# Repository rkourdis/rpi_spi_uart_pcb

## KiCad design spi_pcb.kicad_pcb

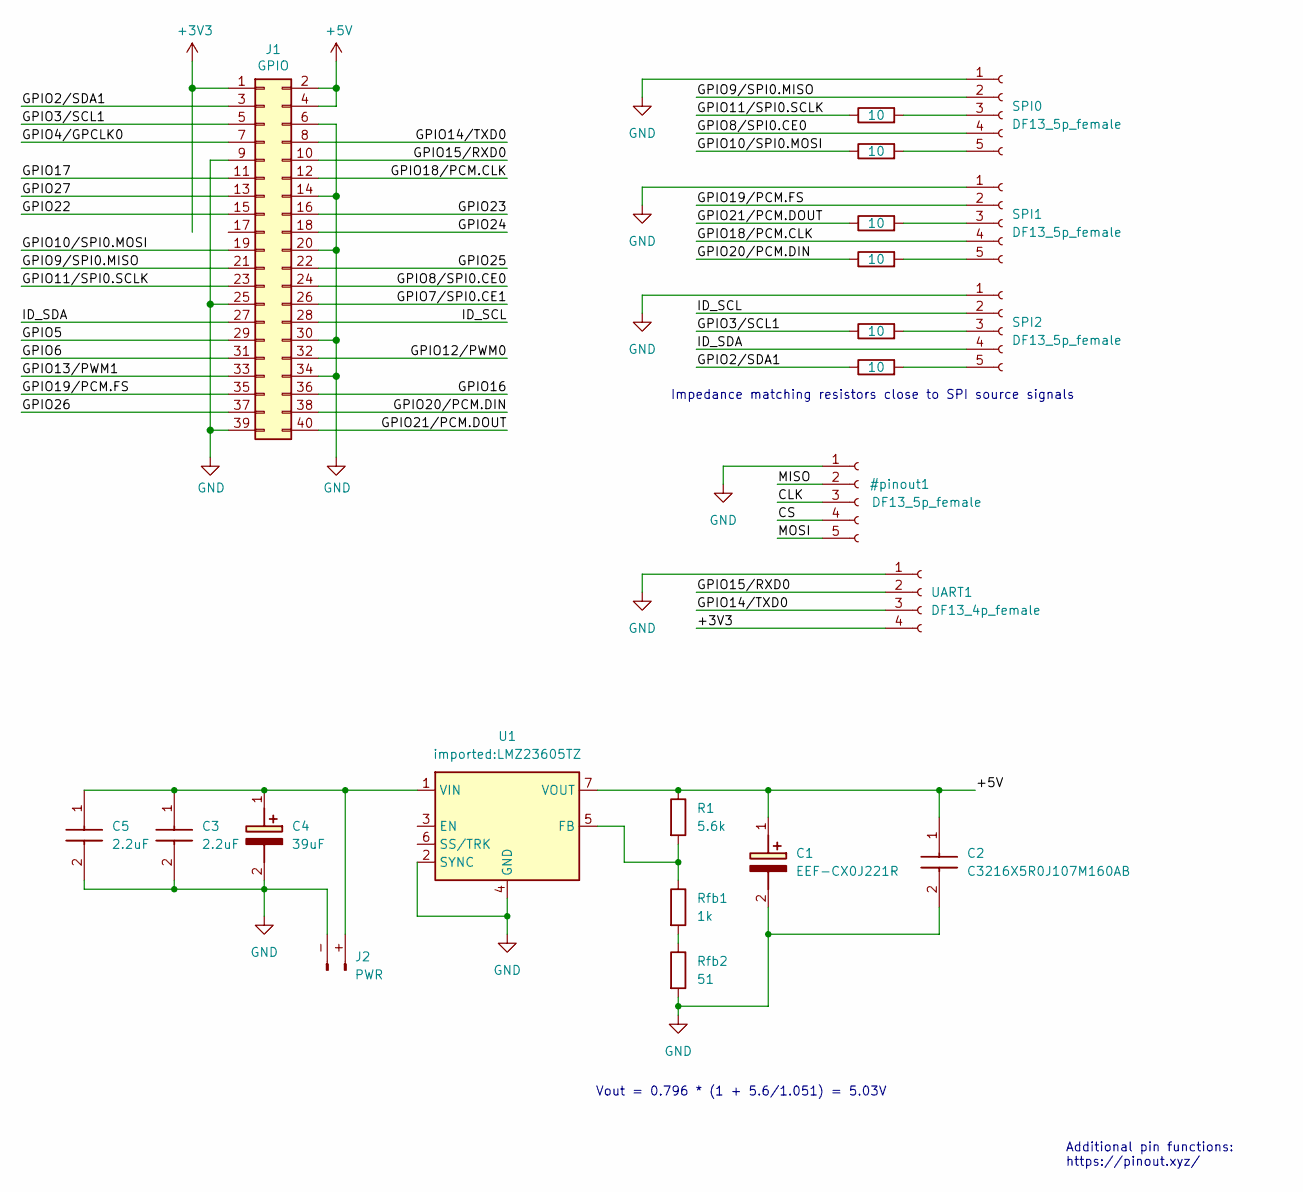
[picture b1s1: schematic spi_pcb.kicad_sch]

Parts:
C1: EEF-CX0J221R; EEFCX0J101R; Mouser Part Number 667-EEF-CX0J221R
C2: C3216X5R0J107M160AB; CAPC3216X180N; Mouser Part Number 810-C3216X5R0J107M
C3, C5: 2.2uF; CAPC1608X90N; Mouser Part Number 81-GRT188R61H225KE3D
C4: 39uF; 16SVPT560M; Manufacturer_Part_Number 50SVPF39M; Mouser Part Number 667-50SVPF39M
J1: GPIO; PinSocket_2x20_P2.54mm_Vertical
J2: PWR; AMASS_XT30PW-M_1x02_P2.50mm_Horizontal
R1: 5.6k; R_0603_1608Metric
R3, R4, R5, R6, R7, R8: 10; R_0402_1005Metric_Pad0.72x0.64mm_HandSolder
Rfb1: 1k; R_0603_1608Metric
Rfb2: 51; R_0603_1608Metric
SPI0, SPI1, SPI2: DF13_5p_female; Hirose_DF13-05P-1.25DS_1x05_P1.25mm_Horizontal
U1: imported:LMZ23605TZ; Texas_NDW-7_TabPin4
UART1: DF13_4p_female; Hirose_DF13-04P-1.25DS_1x04_P1.25mm_Horizontal

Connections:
+3V3: J1.1, UART1.4
+5V: C1.1 (+), C2.1, J1.2, J1.4, R1.1, U1.7 (VOUT)
/GPIO2/SDA1: J1.3, R8.1
/GPIO3/SCL1: J1.5, R7.1
/GPIO4/GPCLK0: J1.7
/GPIO5: J1.29
/GPIO6: J1.31
/GPIO7/SPI0.CE1: J1.26
/GPIO8/SPI0.CE0: J1.24, SPI0.4
/GPIO9/SPI0.MISO: J1.21, SPI0.2
/GPIO10/SPI0.MOSI: J1.19, R4.1
/GPIO11/SPI0.SCLK: J1.23, R3.1
/GPIO12/PWM0: J1.32
/GPIO13/PWM1: J1.33
/GPIO14/TXD0: J1.8, UART1.3
/GPIO15/RXD0: J1.10, UART1.2
/GPIO16: J1.36
/GPIO17: J1.11
/GPIO18/PCM.CLK: J1.12, SPI1.4
/GPIO19/PCM.FS: J1.35, SPI1.2
/GPIO20/PCM.DIN: J1.38, R5.1
/GPIO21/PCM.DOUT: J1.40, R6.1
/GPIO22: J1.15
/GPIO23: J1.16
/GPIO24: J1.18
/GPIO25: J1.22
/GPIO26: J1.37
/GPIO27: J1.13
/ID_SCL: J1.28, SPI2.2
/ID_SDA: J1.27, SPI2.4
GND: C1.2 (-), C2.2, C3.2, C4.2 (-), C5.2, J1.6, J1.9, J1.14, J1.20, J1.25, J1.30, J1.34, J1.39, J2.- (Pin_1), Rfb2.2, SPI0.1, SPI1.1, SPI2.1, U1.2 (SYNC), U1.4 (GND), UART1.1
unnamed: C3.1, C4.1 (+), C5.1, J2.+ (Pin_2), U1.1 (VIN)
unnamed: Rfb1.2, Rfb2.1
unnamed: R3.2, SPI0.3
unnamed: R4.2, SPI0.5
unnamed: R6.2, SPI1.3
unnamed: R5.2, SPI1.5
unnamed: R7.2, SPI2.3
unnamed: R8.2, SPI2.5
unnamed: R1.2, Rfb1.1, U1.5 (FB)

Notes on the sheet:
Additional pin functions: https://pinout.xyz/
Impedance matching resistors close to SPI source signals
Vout = 0.796 * (1 + 5.6/1.051) = 5.03V

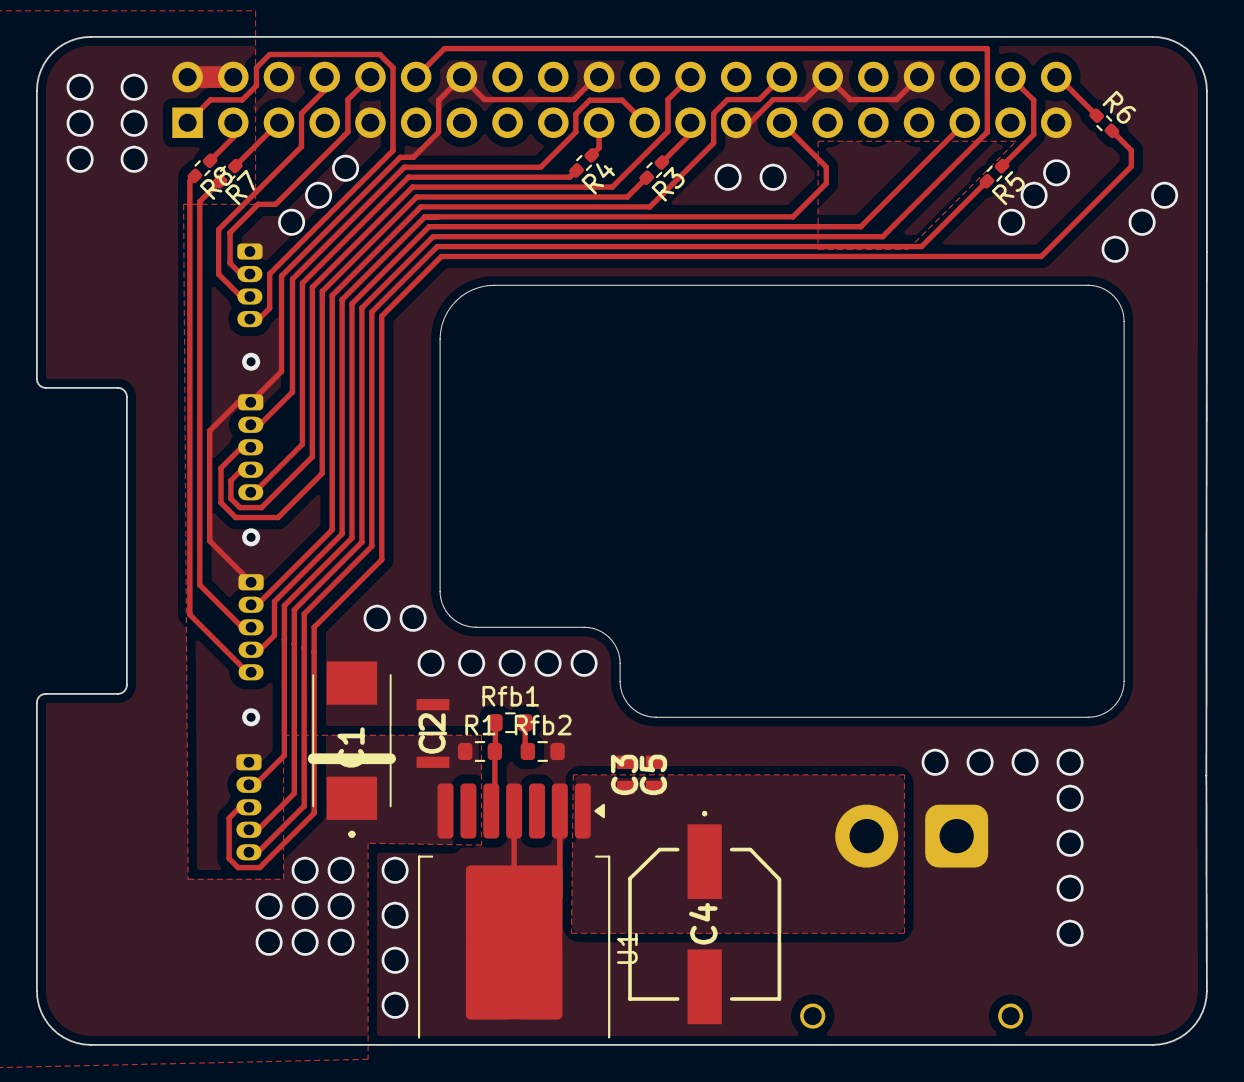
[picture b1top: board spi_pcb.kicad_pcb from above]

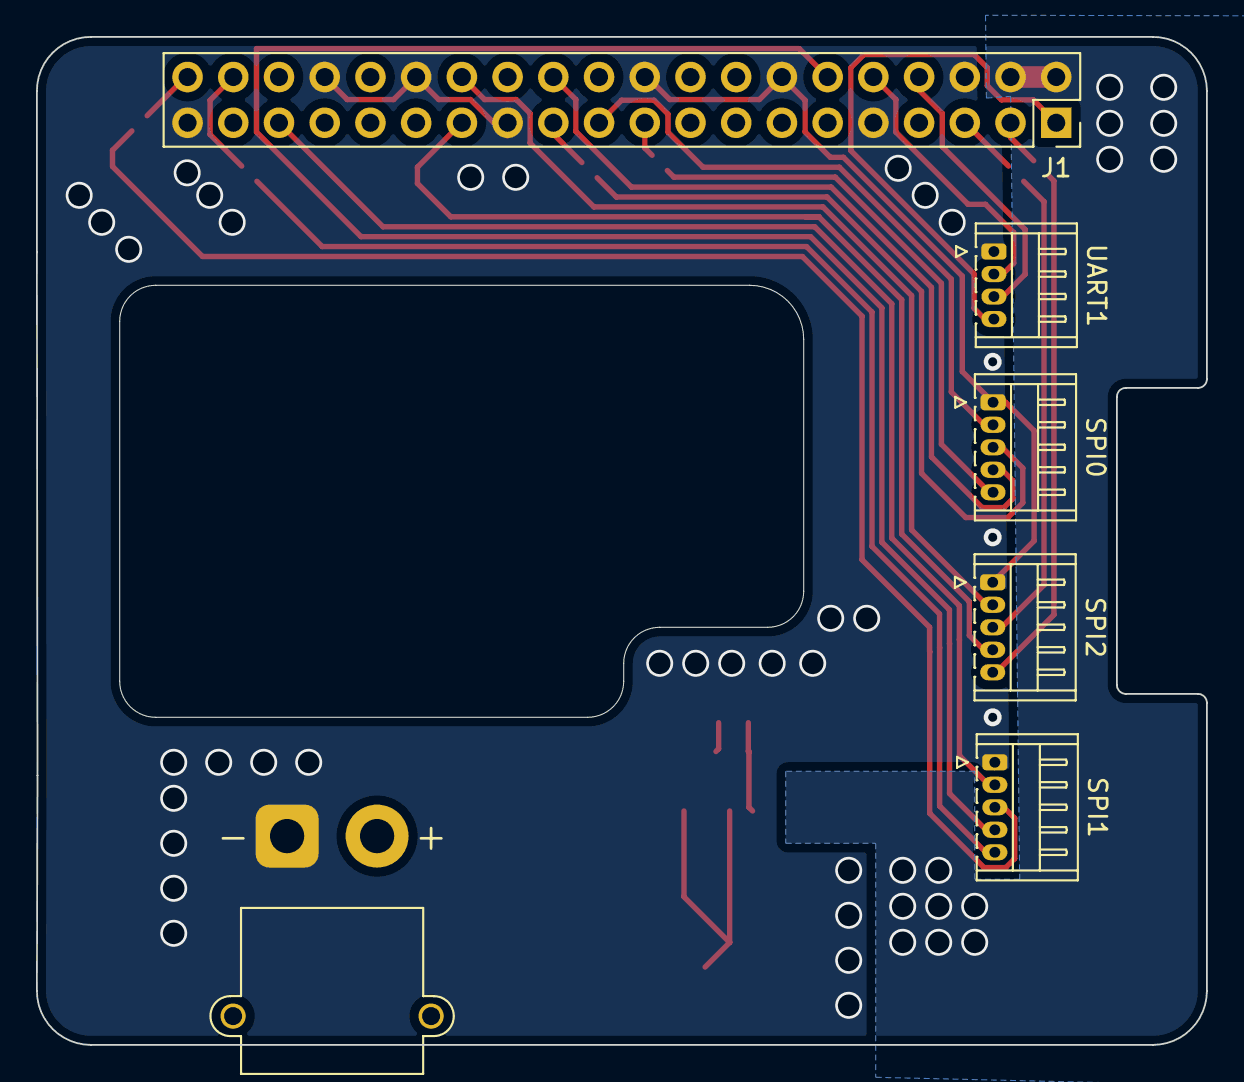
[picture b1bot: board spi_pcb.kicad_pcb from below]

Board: 2 copper layers, 65.0 x 56.0 mm, 21 parts (6 on the bottom side), 26 nets.

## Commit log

2025-06-18 Sent connectors to back plane
2025-06-18 Add copper pours, cooling cutout and correct vias.
2025-06-18 Correct schematic annotations
2025-06-19 Added VCC ceramic filter caps
2025-06-19 Rerouted for 0.25mm copper clearance. Added sample SPI impedance matching resistor.
2025-06-19 Cut cooling hole for Raspberry CPU, redone vias. Added 10 Ohm impedance matching for source SPI signals.
2025-06-19 Fill all areas with copper to reduce CNC time.
2025-06-19 Move power connector a bit closer to centre. Add project library.
2025-06-19 Split feedback resistors into available values.
2025-06-19 Increased via diameter to allow for wire soldering.
2025-06-20 Add information to schematic
